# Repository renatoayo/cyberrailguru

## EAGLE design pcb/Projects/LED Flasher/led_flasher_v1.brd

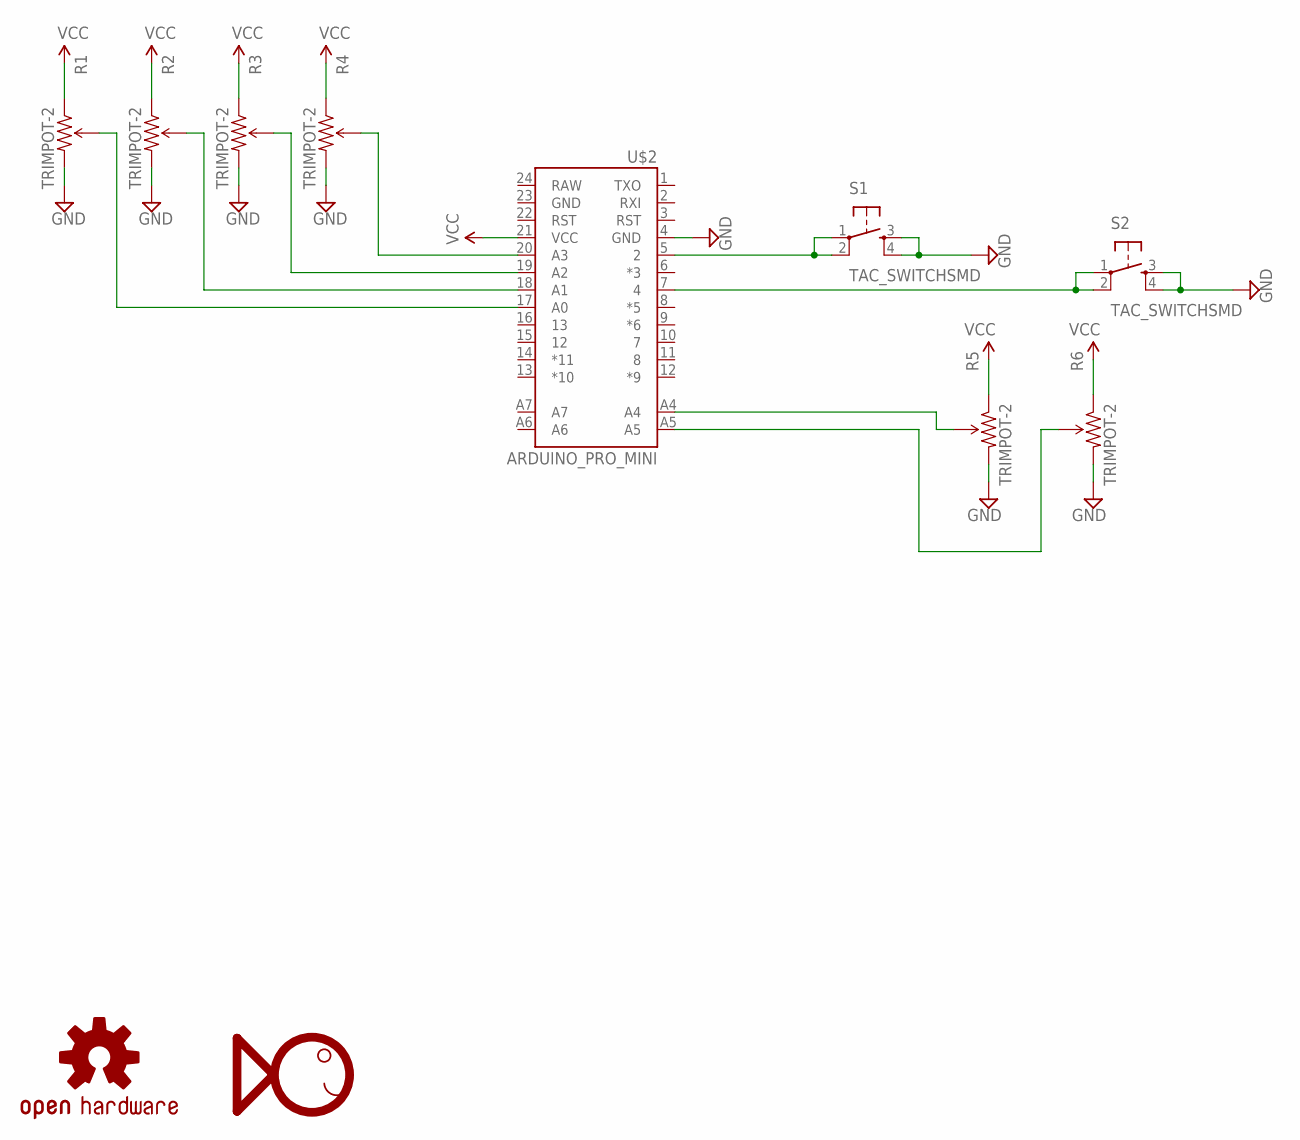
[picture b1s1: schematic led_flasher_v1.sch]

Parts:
LOGO1: OSHW-LOGOS; OSHW-LOGO-S
R1, R2, R3, R4, R5, R6: TRIMPOT-2; TRIMPOT_TC33
S1, S2: TAC_SWITCHSMD; TACTILE-SWITCH-SMD
U$1: FHI_LOGO
U$2: ARDUINO_PRO_MINI

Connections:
GND: R1.3 (CW), R2.3 (CW), R3.3 (CW), R4.3 (CW), R5.3 (CW), R6.3 (CW), S1.3, S1.4, S2.3, S2.4, U$2.4 (GND)
unnamed: R4.2 (WIPER), U$2.20 (A3)
unnamed: R5.2 (WIPER), U$2.A4
unnamed: R6.2 (WIPER), U$2.A5
unnamed: R1.2 (WIPER), U$2.17 (A0)
unnamed: R2.2 (WIPER), U$2.18 (A1)
unnamed: R3.2 (WIPER), U$2.19 (A2)
unnamed: S2.1, S2.2, U$2.7 (4)
unnamed: S1.1, S1.2, U$2.5 (2)
VCC: R1.1 (CCW), R2.1 (CCW), R3.1 (CCW), R4.1 (CCW), R5.1 (CCW), R6.1 (CCW), U$2.21 (VCC)

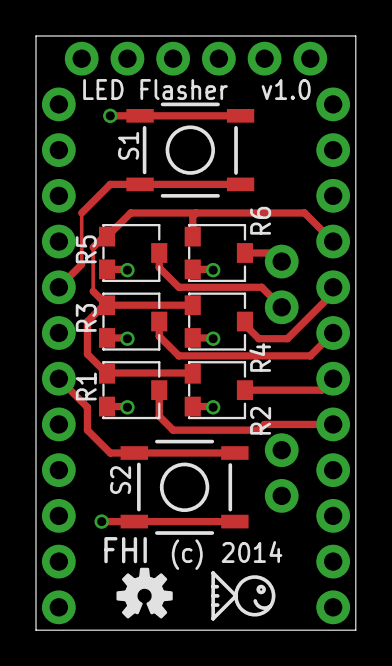
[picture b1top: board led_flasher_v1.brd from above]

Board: 2 copper layers, 17.8 x 33.0 mm, 11 parts (0 on the bottom side), 10 nets.

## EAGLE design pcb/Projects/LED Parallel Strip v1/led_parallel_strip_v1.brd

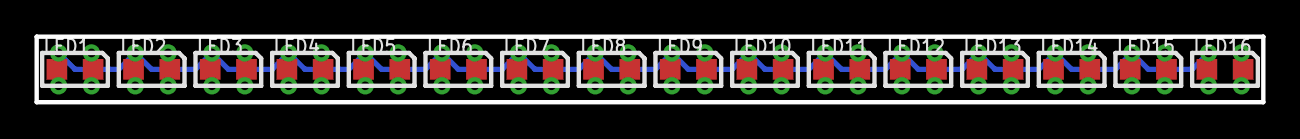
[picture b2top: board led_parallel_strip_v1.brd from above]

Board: 2 copper layers, 71.1 x 3.8 mm, 81 parts (1 on the bottom side), 17 nets.

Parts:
LED1, LED2, LED3, LED4, LED5, LED6, LED7, LED8, LED9, LED10, LED11, LED12, LED13, LED14, LED15, LED16: LED_0805
TP3, TP4, TP5, TP6, TP7, TP8, TP9, TP10, TP11, TP12, TP13, TP14, TP15, TP16, TP17, TP18, TP19, TP20, TP21, TP22, TP23, TP24, TP25, TP26, TP27, TP28, TP29, TP30, TP31, TP32, TP33, TP34: VHS; P1-20
TP37, TP38, TP39, TP41, TP42, TP43, TP44, TP45, TP46, TP47, TP48, TP49, TP50, TP51, TP52, TP53, TP54, TP55, TP56, TP57, TP58, TP59, TP60, TP61, TP62, TP63, TP64, TP65, TP66, TP67, TP68: VLS; P1-20
TP40: VIN; P1-20
U$1: FHI_LOGO

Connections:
VHS1: LED1.C, TP3.TP, TP4.TP
VHS2: LED2.C, TP5.TP, TP6.TP
VHS3: LED3.C, TP7.TP, TP8.TP
VHS4: LED4.C, TP9.TP, TP10.TP
VHS5: LED5.C, TP11.TP, TP12.TP
VHS6: LED6.C, TP13.TP, TP14.TP
VHS7: LED7.C, TP15.TP, TP16.TP
VHS8: LED8.C, TP17.TP, TP18.TP
VHS9: LED9.C, TP19.TP, TP20.TP
VHS10: LED10.C, TP21.TP, TP22.TP
VHS11: LED11.C, TP23.TP, TP24.TP
VHS12: LED12.C, TP25.TP, TP26.TP
VHS13: LED13.C, TP27.TP, TP28.TP
VHS14: LED14.C, TP29.TP, TP30.TP
VHS15: LED15.C, TP31.TP, TP32.TP
VHS16: LED16.C, TP33.TP, TP34.TP
VLS: LED1.A, LED2.A, LED3.A, LED4.A, LED5.A, LED6.A, LED7.A, LED8.A, LED9.A, LED10.A, LED11.A, LED12.A, LED13.A, LED14.A, LED15.A, LED16.A, TP37.TP, TP38.TP, TP39.TP, TP40.TP, TP41.TP, TP42.TP, TP43.TP, TP44.TP, TP45.TP, TP46.TP, TP47.TP, TP48.TP, TP49.TP, TP50.TP, TP51.TP, TP52.TP, TP53.TP, TP54.TP, TP55.TP, TP56.TP, TP57.TP, TP58.TP, TP59.TP, TP60.TP, TP61.TP, TP62.TP, TP63.TP, TP64.TP, TP65.TP, TP66.TP, TP67.TP, TP68.TP

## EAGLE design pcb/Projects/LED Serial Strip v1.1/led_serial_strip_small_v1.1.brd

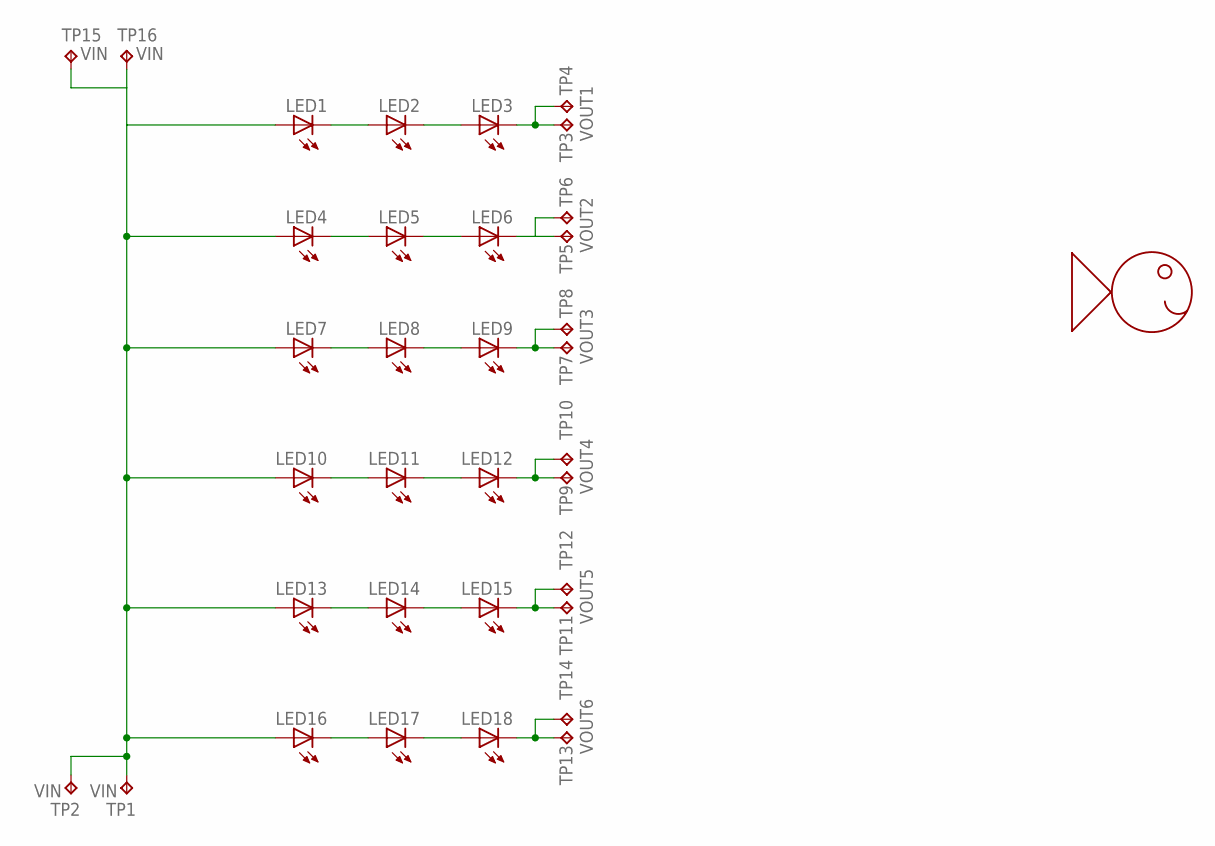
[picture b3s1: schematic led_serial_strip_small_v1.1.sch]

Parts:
LED1, LED2, LED3, LED4, LED5, LED6, LED7, LED8, LED9, LED10, LED11, LED12, LED13, LED14, LED15, LED16, LED17, LED18: LED0805; LED_0805
TP1, TP2, TP15, TP16: VIN; P1-20
TP3, TP4: VOUT1; P1-20
TP5, TP6: VOUT2; P1-20
TP7, TP8: VOUT3; P1-20
TP9, TP10: VOUT4; P1-20
TP11, TP12: VOUT5; P1-20
TP13, TP14: VOUT6; P1-20
U$1: FHI_LOGO

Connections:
unnamed: LED1.C, LED2.A
unnamed: LED2.C, LED3.A
unnamed: LED10.C, LED11.A
unnamed: LED11.C, LED12.A
unnamed: LED8.C, LED9.A
unnamed: LED5.C, LED6.A
unnamed: LED4.C, LED5.A
unnamed: LED7.C, LED8.A
unnamed: LED12.C, TP9.TP, TP10.TP
unnamed: LED16.C, LED17.A
unnamed: LED17.C, LED18.A
unnamed: LED14.C, LED15.A
unnamed: LED13.C, LED14.A
VIN: LED1.A, LED4.A, LED7.A, LED10.A, LED13.A, LED16.A, TP1.TP, TP2.TP, TP15.TP, TP16.TP
VOUT1: LED3.C, TP3.TP, TP4.TP
VOUT2: LED6.C, TP5.TP, TP6.TP
VOUT3: LED9.C, TP7.TP, TP8.TP
VOUT5: LED15.C, TP11.TP, TP12.TP
VOUT6: LED18.C, TP13.TP, TP14.TP

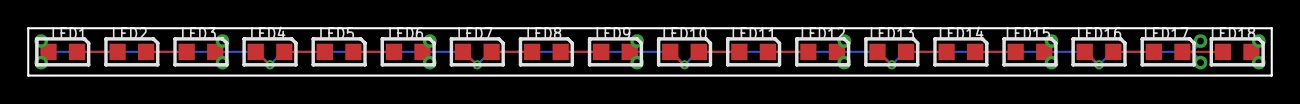
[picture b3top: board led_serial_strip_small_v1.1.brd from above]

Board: 2 copper layers, 91.4 x 3.5 mm, 35 parts (1 on the bottom side), 19 nets.

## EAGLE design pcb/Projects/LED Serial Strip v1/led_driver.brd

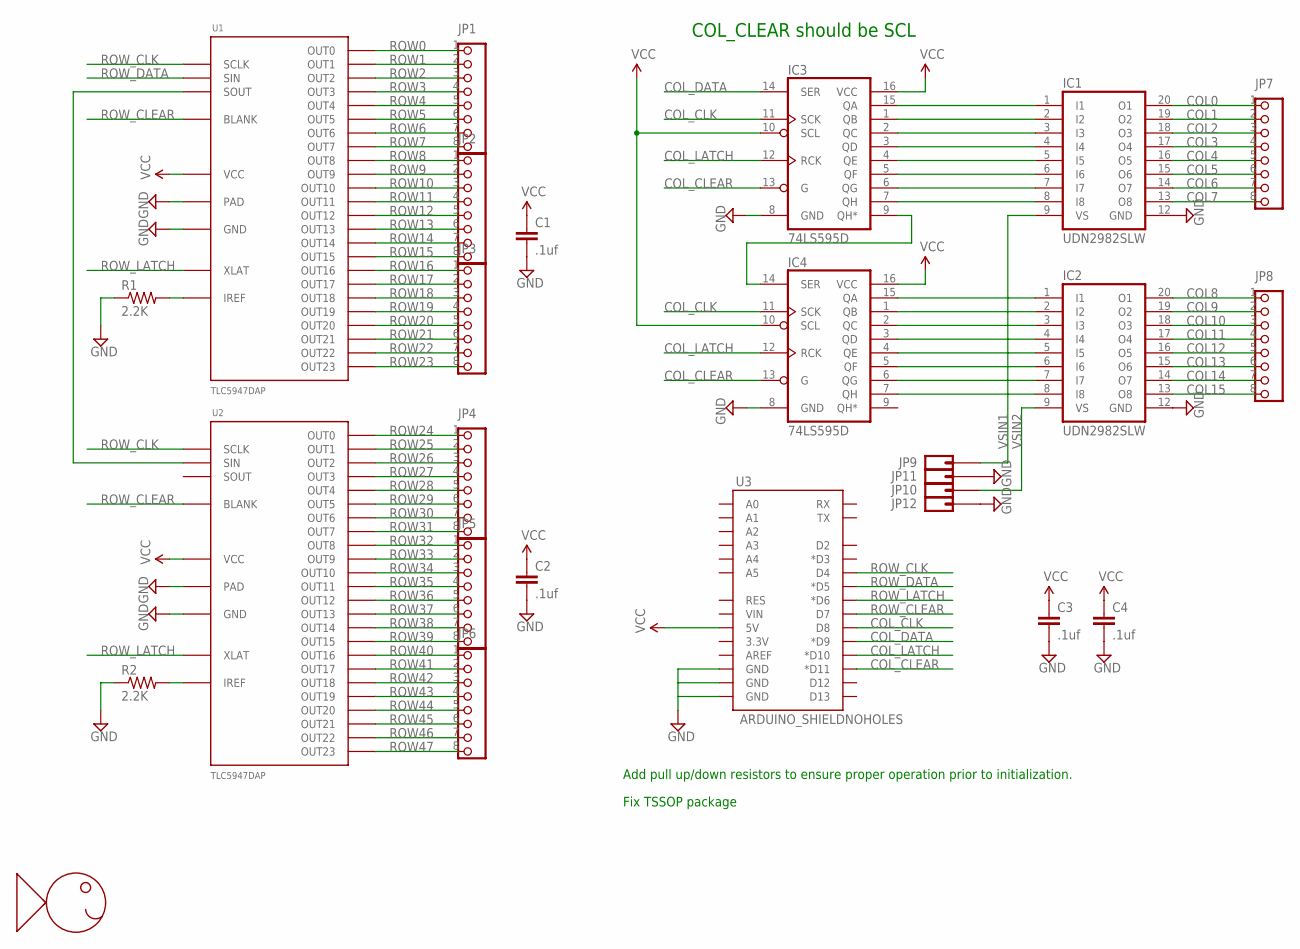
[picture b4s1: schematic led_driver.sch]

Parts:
C1, C2, C3, C4: .1uf; 0603-CAP
IC1, IC2: UDN2982SLW; SO20W
IC3, IC4: 74LS595D; SO16
JP1, JP2, JP3, JP4, JP5, JP6, JP7, JP8: PINHD-1X8; 1X08
JP9, JP10, JP11, JP12: HEADER_01PTH; 1X01
R1, R2: 2.2K; 0603-RES
U1, U2: TLC5947DAP; HTSSOP32DAP
U3: ARDUINO_SHIELDNOHOLES; DUEMILANOVE_SHIELD_NOHOLES
U$1: FHI_LOGO

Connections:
COL0: IC1.20 (O1), JP7.1
COL1: IC1.19 (O2), JP7.2
COL2: IC1.18 (O3), JP7.3
COL3: IC1.17 (O4), JP7.4
COL4: IC1.16 (O5), JP7.5
COL5: IC1.15 (O6), JP7.6
COL6: IC1.14 (O7), JP7.7
COL7: IC1.13 (O8), JP7.8
COL8: IC2.20 (O1), JP8.1
COL9: IC2.19 (O2), JP8.2
COL10: IC2.18 (O3), JP8.3
COL11: IC2.17 (O4), JP8.4
COL12: IC2.16 (O5), JP8.5
COL13: IC2.15 (O6), JP8.6
COL14: IC2.14 (O7), JP8.7
COL15: IC2.13 (O8), JP8.8
COL_CLEAR: IC3.13 (G), IC4.13 (G), U3.D11 (*D11)
COL_CLK: IC3.11 (SCK), IC4.11 (SCK), U3.D8
COL_DATA: IC3.14 (SER), U3.D9 (*D9)
COL_LATCH: IC3.12 (RCK), IC4.12 (RCK), U3.D10 (*D10)
GND: C1.2, C2.2, C3.2, C4.2, IC1.12 (GND), IC2.12 (GND), IC3.8 (GND), IC4.8 (GND), JP11.1, JP12.1, R1.1, R2.1, U1.1 (GND), U1.EXP (PAD), U2.1 (GND), U2.EXP (PAD), U3.GND@0 (GND), U3.GND@1 (GND), U3.GND@2 (GND)
unnamed: IC1.1 (I1), IC3.15 (QA)
unnamed: IC1.2 (I2), IC3.1 (QB)
unnamed: IC1.3 (I3), IC3.2 (QC)
unnamed: IC1.4 (I4), IC3.3 (QD)
unnamed: IC1.5 (I5), IC3.4 (QE)
unnamed: IC1.6 (I6), IC3.5 (QF)
unnamed: IC1.7 (I7), IC3.6 (QG)
unnamed: IC1.8 (I8), IC3.7 (QH)
unnamed: IC3.9 (QH*), IC4.14 (SER)
unnamed: IC2.1 (I1), IC4.15 (QA)
unnamed: IC2.2 (I2), IC4.1 (QB)
unnamed: IC2.3 (I3), IC4.2 (QC)
unnamed: IC2.4 (I4), IC4.3 (QD)
unnamed: IC2.5 (I5), IC4.4 (QE)
unnamed: IC2.6 (I6), IC4.5 (QF)
unnamed: IC2.7 (I7), IC4.6 (QG)
unnamed: IC2.8 (I8), IC4.7 (QH)
unnamed: R2.2, U2.31 (IREF)
unnamed: R1.2, U1.31 (IREF)
unnamed: U1.29 (SOUT), U2.4 (SIN)
ROW0: JP1.1, U1.5 (OUT0)
ROW1: JP1.2, U1.6 (OUT1)
ROW2: JP1.3, U1.7 (OUT2)
ROW3: JP1.4, U1.8 (OUT3)
ROW4: JP1.5, U1.9 (OUT4)
ROW5: JP1.6, U1.10 (OUT5)
ROW6: JP1.7, U1.11 (OUT6)
ROW7: JP1.8, U1.12 (OUT7)
ROW8: JP2.1, U1.13 (OUT8)
ROW9: JP2.2, U1.14 (OUT9)
ROW10: JP2.3, U1.15 (OUT10)
ROW11: JP2.4, U1.16 (OUT11)
ROW12: JP2.5, U1.17 (OUT12)
ROW13: JP2.6, U1.18 (OUT13)
ROW14: JP2.7, U1.19 (OUT14)
ROW15: JP2.8, U1.20 (OUT15)
ROW16: JP3.1, U1.21 (OUT16)
ROW17: JP3.2, U1.22 (OUT17)
ROW18: JP3.3, U1.23 (OUT18)
ROW19: JP3.4, U1.24 (OUT19)
ROW20: JP3.5, U1.25 (OUT20)
ROW21: JP3.6, U1.26 (OUT21)
ROW22: JP3.7, U1.27 (OUT22)
ROW23: JP3.8, U1.28 (OUT23)
ROW24: JP4.1, U2.5 (OUT0)
ROW25: JP4.2, U2.6 (OUT1)
ROW26: JP4.3, U2.7 (OUT2)
ROW27: JP4.4, U2.8 (OUT3)
ROW28: JP4.5, U2.9 (OUT4)
ROW29: JP4.6, U2.10 (OUT5)
ROW30: JP4.7, U2.11 (OUT6)
ROW31: JP4.8, U2.12 (OUT7)
ROW32: JP5.1, U2.13 (OUT8)
ROW33: JP5.2, U2.14 (OUT9)
ROW34: JP5.3, U2.15 (OUT10)
ROW35: JP5.4, U2.16 (OUT11)
ROW36: JP5.5, U2.17 (OUT12)
ROW37: JP5.6, U2.18 (OUT13)
ROW38: JP5.7, U2.19 (OUT14)
ROW39: JP5.8, U2.20 (OUT15)
ROW40: JP6.1, U2.21 (OUT16)
ROW41: JP6.2, U2.22 (OUT17)
ROW42: JP6.3, U2.23 (OUT18)
ROW43: JP6.4, U2.24 (OUT19)
ROW44: JP6.5, U2.25 (OUT20)
ROW45: JP6.6, U2.26 (OUT21)
ROW46: JP6.7, U2.27 (OUT22)
ROW47: JP6.8, U2.28 (OUT23)
ROW_CLEAR: U1.2 (BLANK), U2.2 (BLANK), U3.D7
ROW_CLK: U1.3 (SCLK), U2.3 (SCLK), U3.D4
ROW_DATA: U1.4 (SIN), U3.D5 (*D5)
ROW_LATCH: U1.30 (XLAT), U2.30 (XLAT), U3.D6 (*D6)
VCC: C1.1, C2.1, C3.1, C4.1, IC3.10 (SCL), IC3.16 (VCC), IC4.10 (SCL), IC4.16 (VCC), U1.32 (VCC), U2.32 (VCC), U3.5V
VSIN1: IC1.9 (VS), JP9.1
VSIN2: IC2.9 (VS), JP10.1

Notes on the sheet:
COL_CLEAR should be SCL
Add pull up/down resistors to ensure proper operation prior to initialization.
Fix TSSOP package

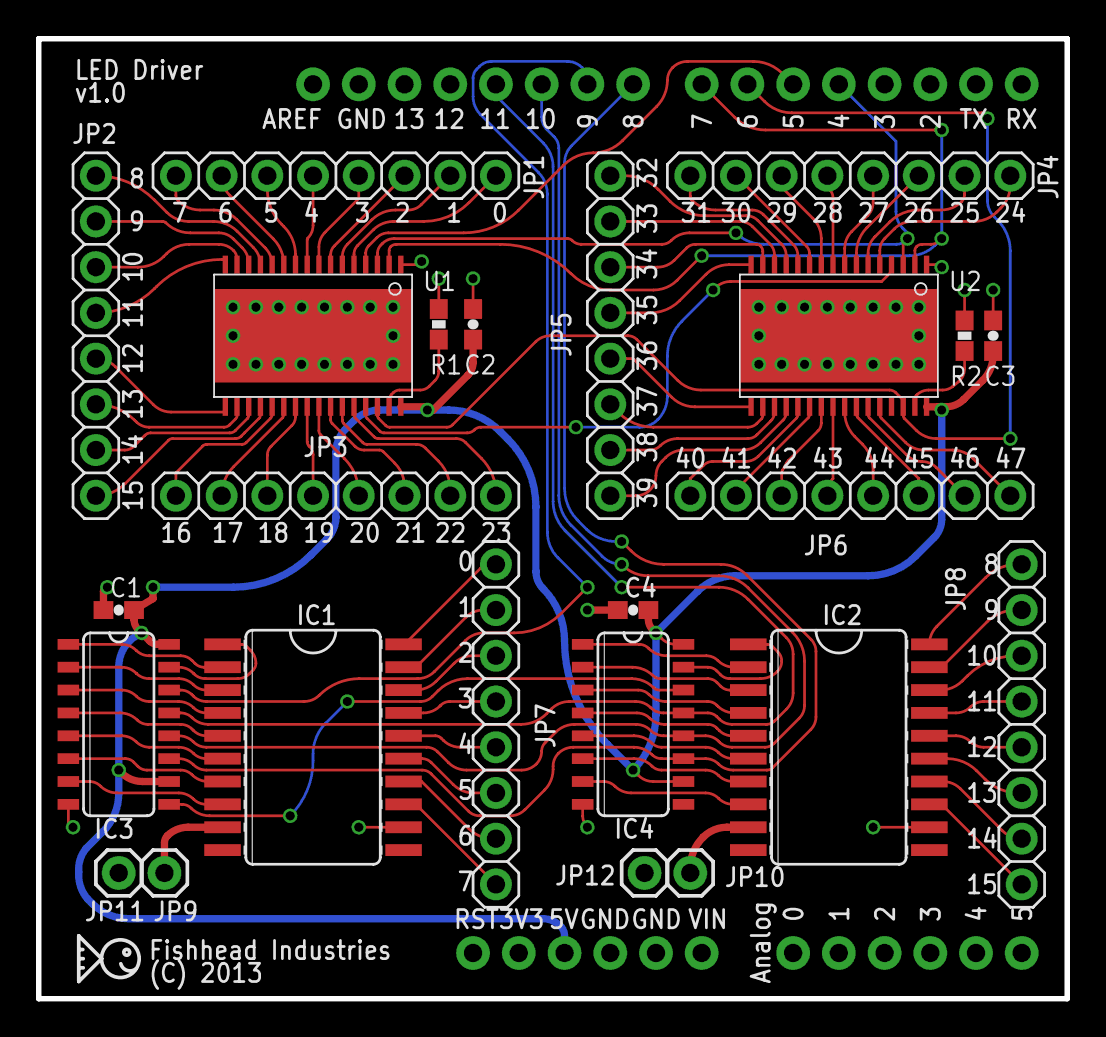
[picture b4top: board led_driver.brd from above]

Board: 2 copper layers, 57.1 x 53.3 mm, 26 parts (0 on the bottom side), 96 nets.

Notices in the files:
pcb/Projects/LED Parallel Strip v1/led_parallel_strip_v1.brd:
(C) 2014
pcb/Projects/LED Serial Strip v1.1/led_serial_strip_small_v1.1.brd:
FHI (C) 2014
pcb/Projects/LED Serial Strip v1/led_driver.brd:
(C) 2013
parts and their libraries:
SparkFun-Aesthetics: Licensing: CC v3.0 Share-Alike You are welcome to use this library for commercial purposes.
